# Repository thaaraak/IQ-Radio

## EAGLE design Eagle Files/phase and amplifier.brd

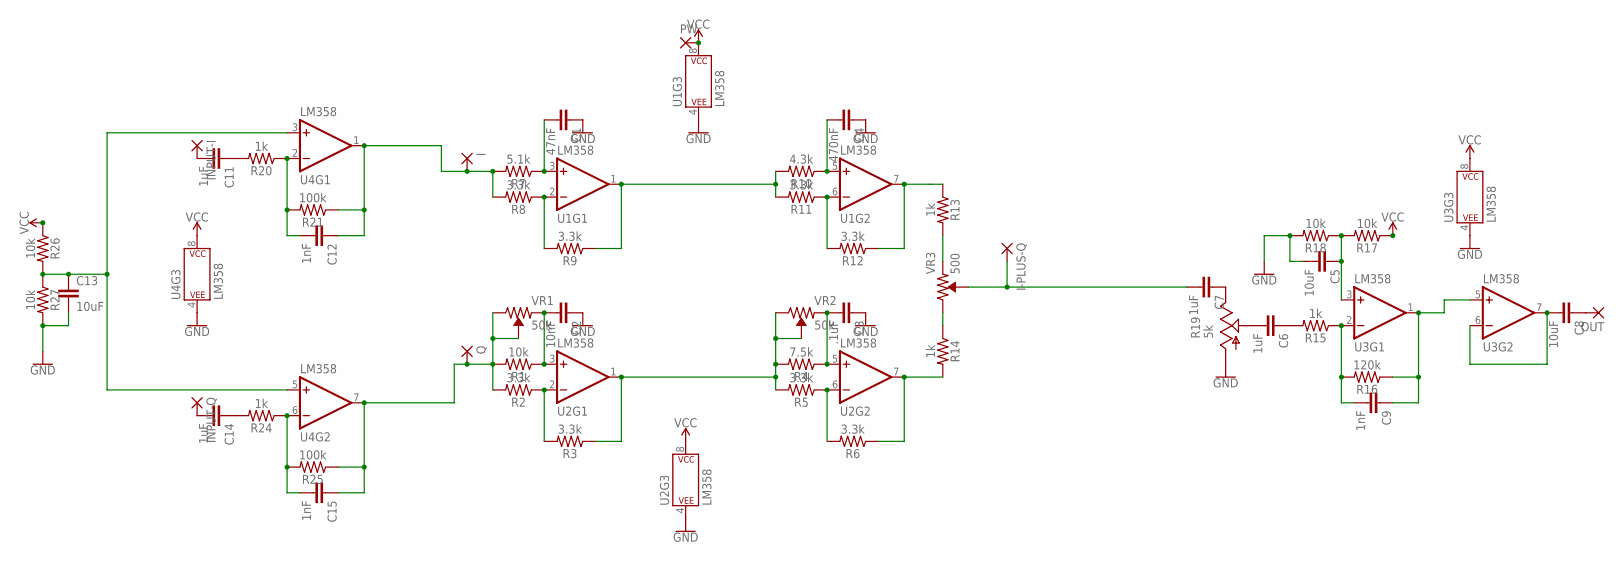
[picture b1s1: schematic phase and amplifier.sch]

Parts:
C1: 47nF; C5B3.5
C2: 10nF; C5B3.5
C3: .1uF; C5B3.5
C4: 470nF; C5B3.5
C5, C8, C13: 10uF; C5B3.5
C6, C7, C11, C14: 1uF; C5B3.5
C9, C12, C15: 1nF; C5B3.5
I: 2,54/1,1
I-PLUS-Q: 2,54/1,1
INPUT-I: 2,54/1,1
INPUT-Q: 2,54/1,1
OUT: 2,54/1,1
PW: 2,54/1,1
Q: 2,54/1,1
R1, R17, R18, R26, R27: 10k; AXIAL-0.3
R2, R3, R5, R6, R8, R9, R11, R12: 3.3k; AXIAL-0.3
R4: 7.5k; AXIAL-0.3
R7: 5.1k; AXIAL-0.3
R10: 4.3k; AXIAL-0.3
R13, R14, R15, R20, R24: 1k; AXIAL-0.3
R16: 120k; AXIAL-0.3
R19: 5k; B25V
R21, R25: 100k; AXIAL-0.3
U1, U2, U3, U4: LM358; DIP08
VR1, VR2: 50k; TRIMPOT-PTH-3386U
VR3: 500; TRIMPOT-PTH-3386U

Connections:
GND: C1.1, C2.1, C3.1, C4.1, C5.2, C13.2, R18.P$2 (2), R19.A, R27.P$2 (2), U1.4 (P$V-), U2.4 (P$V-), U3.4 (P$V-), U4.4 (P$V-)
unnamed: C2.2, R1.P$1 (1), U2.3 (+IN), VR1.1 (CCW)
unnamed: R2.P$1 (1), R3.P$2 (2), U2.2 (-IN)
unnamed: R3.P$1 (1), R4.P$2 (2), R5.P$2 (2), U2.1 (OUT), VR2.2 (WIPER), VR2.3 (CW)
unnamed: C13.1, R26.P$2 (2), R27.P$1 (1), U4.3 (+IN), U4.5 (+IN)
unnamed: C3.2, R4.P$1 (1), U2.5 (+IN), VR2.1 (CCW)
unnamed: R5.P$1 (1), R6.P$2 (2), U2.6 (-IN)
unnamed: R8.P$1 (1), R9.P$2 (2), U1.2 (-IN)
unnamed: R6.P$1 (1), R14.P$2 (2), U2.7 (OUT)
unnamed: C1.2, R7.P$1 (1), U1.3 (+IN)
unnamed: C14.2, INPUT-Q.1
unnamed: C4.2, R10.P$1 (1), U1.5 (+IN)
unnamed: R9.P$1 (1), R10.P$2 (2), R11.P$2 (2), U1.1 (OUT)
unnamed: R11.P$1 (1), R12.P$2 (2), U1.6 (-IN)
unnamed: R13.P$2 (2), VR3.1 (CCW)
unnamed: R12.P$1 (1), R13.P$1 (1), U1.7 (OUT)
unnamed: R14.P$1 (1), VR3.3 (CW)
unnamed: C7.2, I-PLUS-Q.1, VR3.2 (WIPER)
unnamed: C9.1, R16.P$1 (1), U3.1 (OUT), U3.5 (+IN)
unnamed: C9.2, R15.P$1 (1), R16.P$2 (2), U3.2 (-IN)
unnamed: C5.1, R17.P$2 (2), R18.P$1 (1), U3.3 (+IN)
unnamed: C6.1, R15.P$2 (2)
unnamed: C6.2, R19.S
unnamed: C7.1, R19.E
unnamed: C12.1, I.1, R7.P$2 (2), R8.P$2 (2), R21.P$1 (1), U4.1 (OUT)
unnamed: C8.2, U3.6 (-IN), U3.7 (OUT)
unnamed: C8.1, OUT.1
unnamed: C12.2, R20.P$1 (1), R21.P$2 (2), U4.2 (-IN)
unnamed: C11.2, INPUT-I.1
unnamed: C11.1, R20.P$2 (2)
unnamed: C15.1, Q.1, R1.P$2 (2), R2.P$2 (2), R25.P$1 (1), U4.7 (OUT), VR1.2 (WIPER), VR1.3 (CW)
unnamed: C15.2, R24.P$1 (1), R25.P$2 (2), U4.6 (-IN)
unnamed: C14.1, R24.P$2 (2)
VCC: PW.1, R17.P$1 (1), R26.P$1 (1), U1.8 (P$V+), U2.8 (P$V+), U3.8 (P$V+), U4.8 (P$V+)

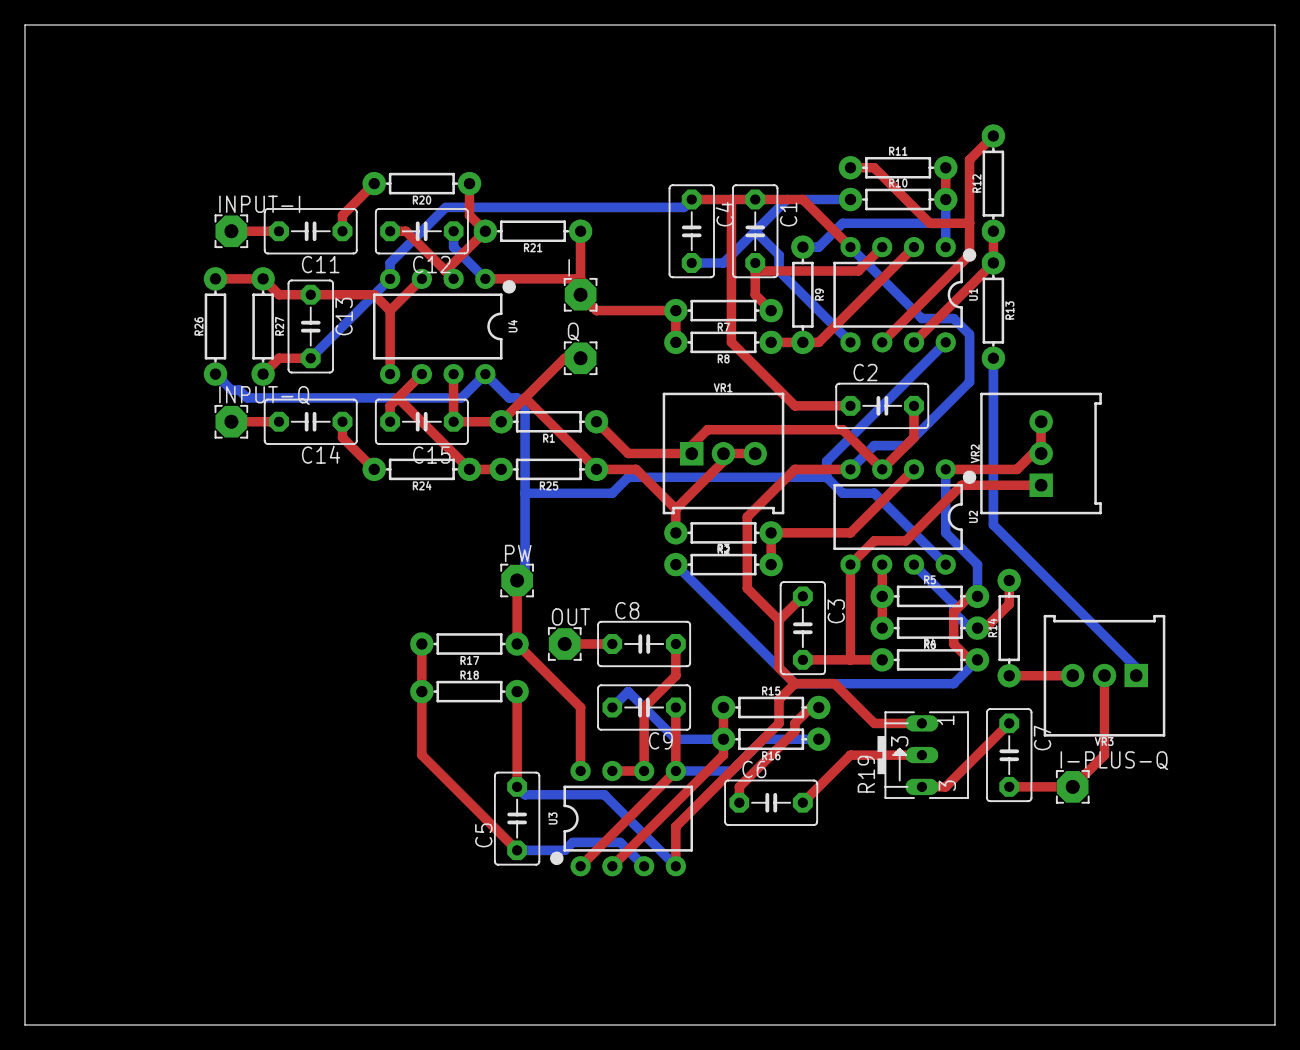
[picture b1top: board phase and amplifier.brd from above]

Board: 2 copper layers, 100.0 x 80.0 mm, 53 parts (0 on the bottom side), 34 nets.

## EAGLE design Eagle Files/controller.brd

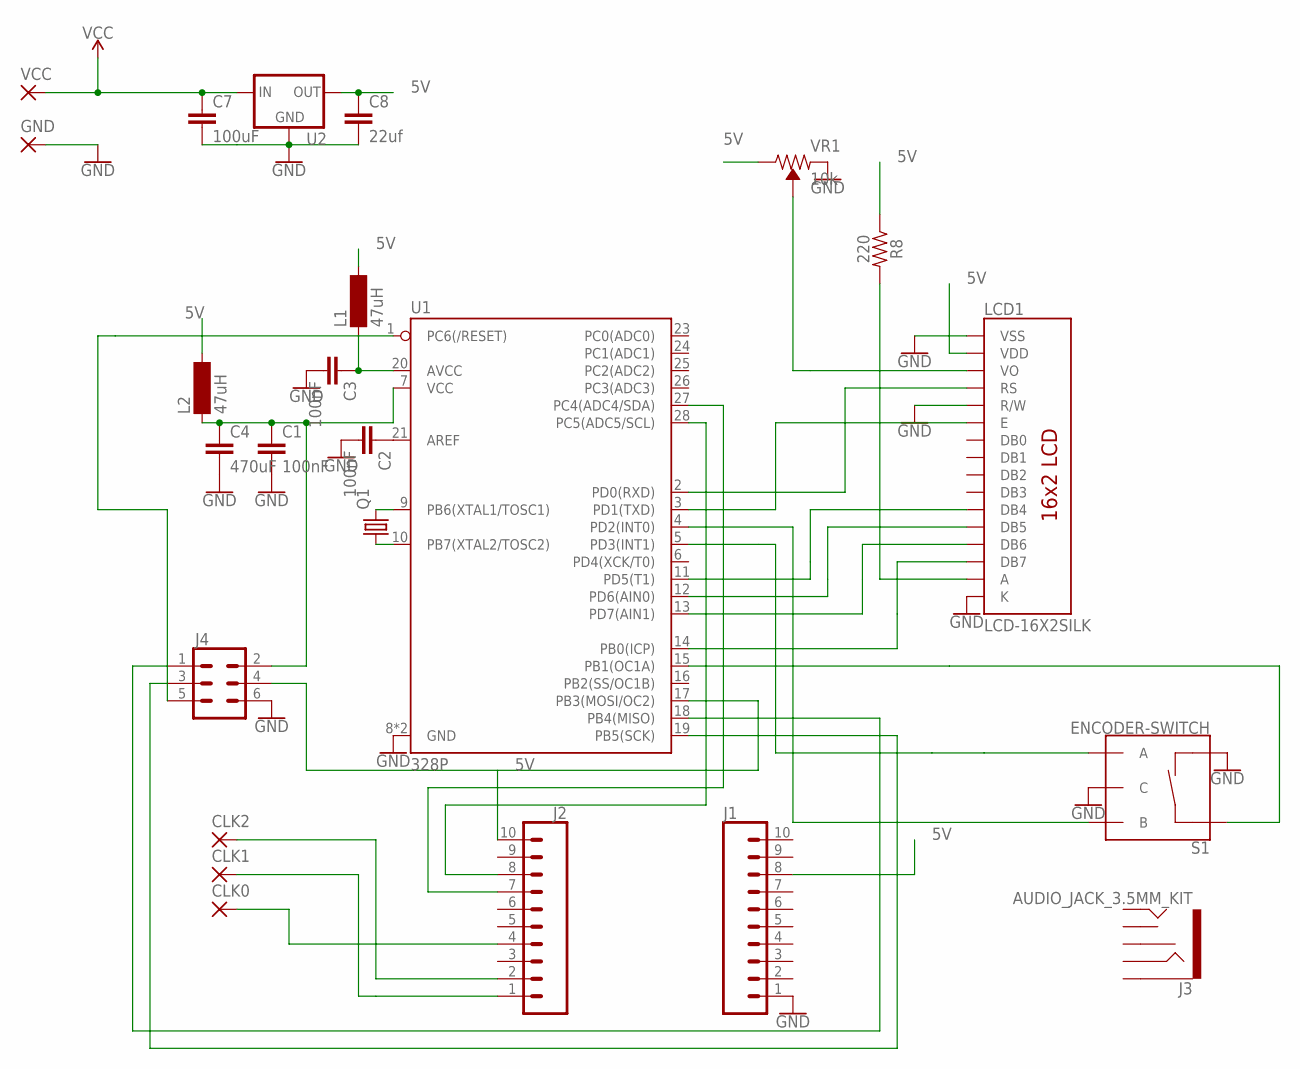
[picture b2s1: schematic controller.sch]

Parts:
C1, C2, C3: 100nF; C5B3.5
C4: 470uF; C5B3.5
C7: 100uF; C5B3.5
C8: 22uf; C5B3.5
CLK0, CLK1, CLK2: 3,17/1,1
GND: 3,17/1,1
J1, J2: CONN_10NO_SILK_PTH_FEMALE; 1X10_NO_SILK
J3: AUDIO_JACK_3.5MM_KIT; AUDIO-JACK-KIT
J4: CONN_03X2NO_SILK; 2X3-NS
L1, L2: 47uH; BS75
LCD1: LCD-16X2SILK; LCD-16X2
Q1: CRYTALHC49S; HC49/S
R8: 220; AXIAL-0.3
S1: ENCODER-SWITCH; ROTARY_ENC_PLAIN
U1: 328P; DIP28
U2: V_REG_78XXSINK; TO220-IGO
VCC: 3,17/1,1
VR1: 10k; TRIMPOT-PTH-3386U

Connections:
5V: C8.1, J1.8, J2.10, L1.2, L2.2, LCD1.2 (VDD), R8.P$1 (1), U2.OUT, VR1.3 (CW)
GND: C1.2, C2.2, C3.2, C4.2, C7.2, C8.2, GND.1, J1.1, J4.6, LCD1.1 (VSS), LCD1.5 (R/W), LCD1.16 (K), S1.C, S1.SW-, U1.8 (GND), U1.22 (GND), U2.GND, VR1.1 (CCW)
unnamed: C2.1, U1.21 (AREF)
unnamed: Q1.2, U1.9 (PB6(XTAL1/TOSC1))
unnamed: Q1.1, U1.10 (PB7(XTAL2/TOSC2))
unnamed: C1.1, C4.1, J4.2, L2.1, U1.7 (VCC)
unnamed: LCD1.14 (DB7), U1.14 (PB0(ICP))
unnamed: LCD1.13 (DB6), U1.13 (PD7(AIN1))
unnamed: S1.SW+, U1.15 (PB1(OC1A))
unnamed: LCD1.4 (RS), U1.2 (PD0(RXD))
unnamed: LCD1.12 (DB5), U1.12 (PD6(AIN0))
unnamed: LCD1.11 (DB4), U1.11 (PD5(T1))
unnamed: LCD1.3 (VO), VR1.2 (WIPER)
unnamed: LCD1.15 (A), R8.P$2 (2)
unnamed: CLK1.1, J2.1
unnamed: CLK2.1, J2.2
unnamed: CLK0.1, J2.4
unnamed: J2.8, U1.28 (PC5(ADC5/SCL))
unnamed: J2.7, U1.27 (PC4(ADC4/SDA))
unnamed: S1.A, U1.5 (PD3(INT1))
unnamed: S1.B, U1.4 (PD2(INT0))
unnamed: LCD1.6 (E), U1.3 (PD1(TXD))
unnamed: C3.1, L1.1, U1.20 (AVCC)
unnamed: J4.4, U1.17 (PB3(MOSI/OC2))
unnamed: J4.1, U1.18 (PB4(MISO))
unnamed: J4.3, U1.19 (PB5(SCK))
unnamed: J4.5, U1.1 (PC6(/RESET))
VCC: C7.1, U2.IN, VCC.1

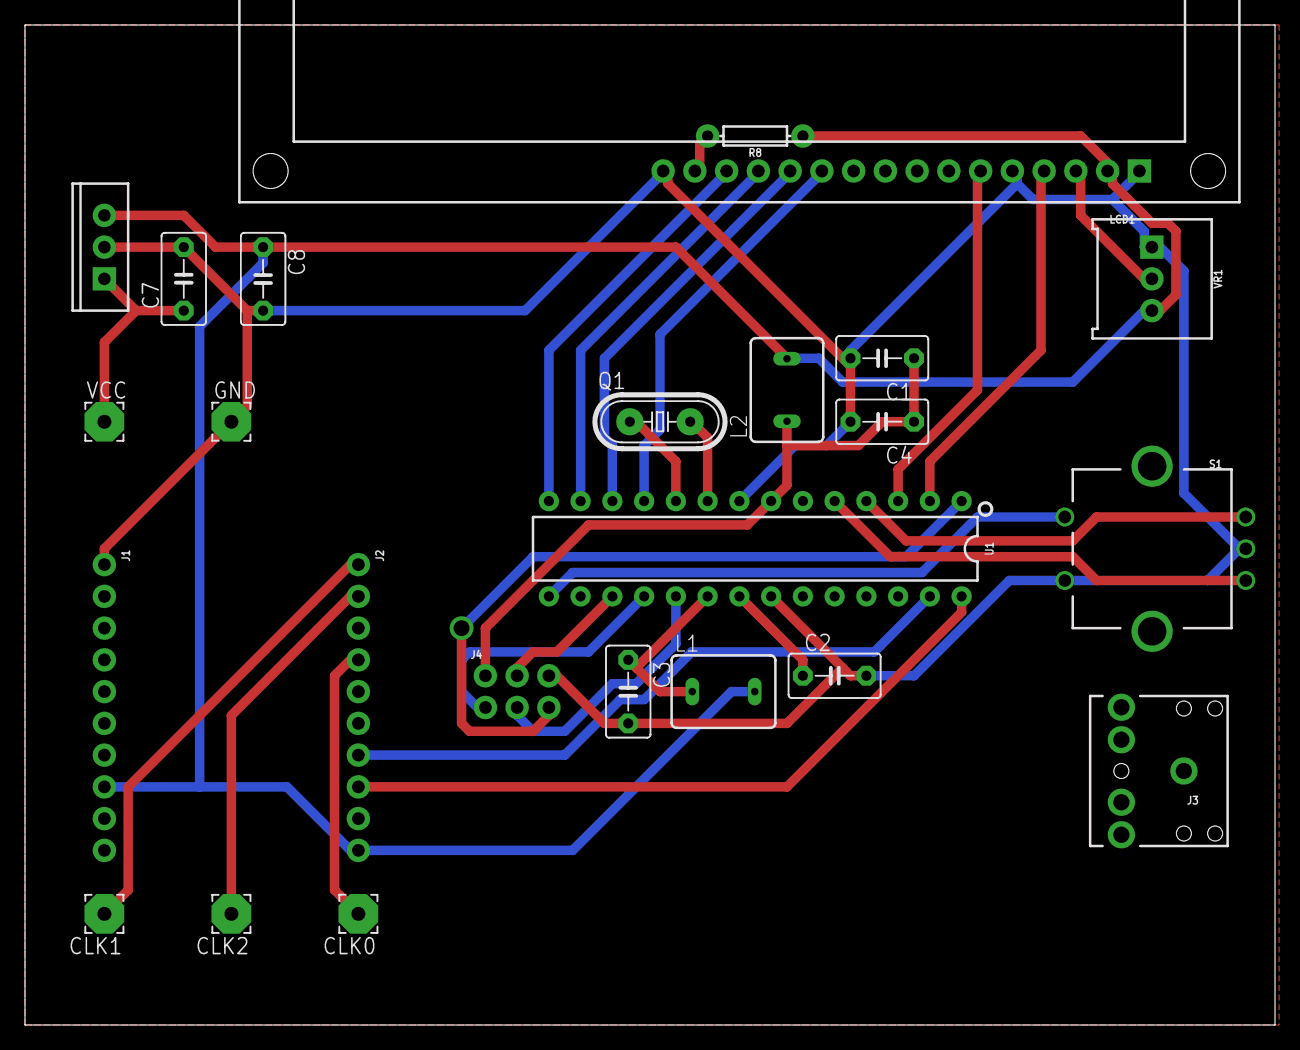
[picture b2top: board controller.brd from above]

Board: 2 copper layers, 100.0 x 80.0 mm, 24 parts (0 on the bottom side), 28 nets.

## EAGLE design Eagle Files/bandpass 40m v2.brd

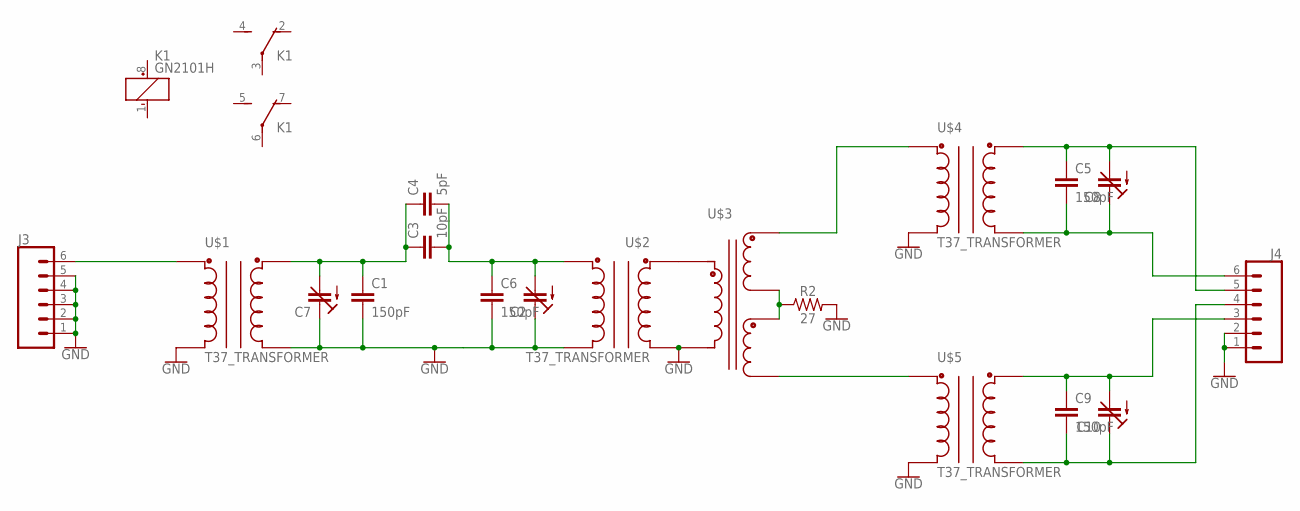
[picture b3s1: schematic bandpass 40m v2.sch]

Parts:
C1, C5, C6, C9: 150pF; C5B3.5
C2, C7, C8, C10: C-TRIMMTZ03; CTRIMTZ03
C3: 10pF; C5B3.5
C4: 5pF; C5B3.5
J3, J4: CONN_06SILK_FEMALE_PTH; 1X06
K1: GN2101H; GN
R2: 27; AXIAL-0.3
U$1, U$2, U$4, U$5: T37_TRANSFORMER
U$3: T50_SPLITTER

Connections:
GND: C1.2, C2.1 (E), C6.2, C7.1 (E), J3.1, J3.2, J3.3, J3.4, J3.5, J4.1, J4.2, R2.P$2 (2), U$1.C1A, U$1.C2A, U$2.C1A, U$2.C2A, U$3.C1A, U$4.C1A, U$5.C1A
GND1: C5.2, C8.1 (E), J4.6, U$4.C2A
GND2: C9.2, C10.1 (E), J4.4, U$5.C2A
unnamed: C1.1, C3.1, C4.1, C7.2 (A), U$1.C2B
unnamed: J3.6, U$1.C1B
unnamed: C2.2 (A), C3.2, C4.2, C6.1, U$2.C2B
unnamed: U$2.C1B, U$3.C1B
unnamed: U$3.C3B (C2B), U$4.C1B
unnamed: R2.P$1 (1), U$3.C2A (C3B), U$3.C3A (C2A)
unnamed: U$3.C2B (C3A), U$5.C1B
unnamed: C5.1, C8.2 (A), J4.5, U$4.C2B
unnamed: C9.1, C10.2 (A), J4.3, U$5.C2B

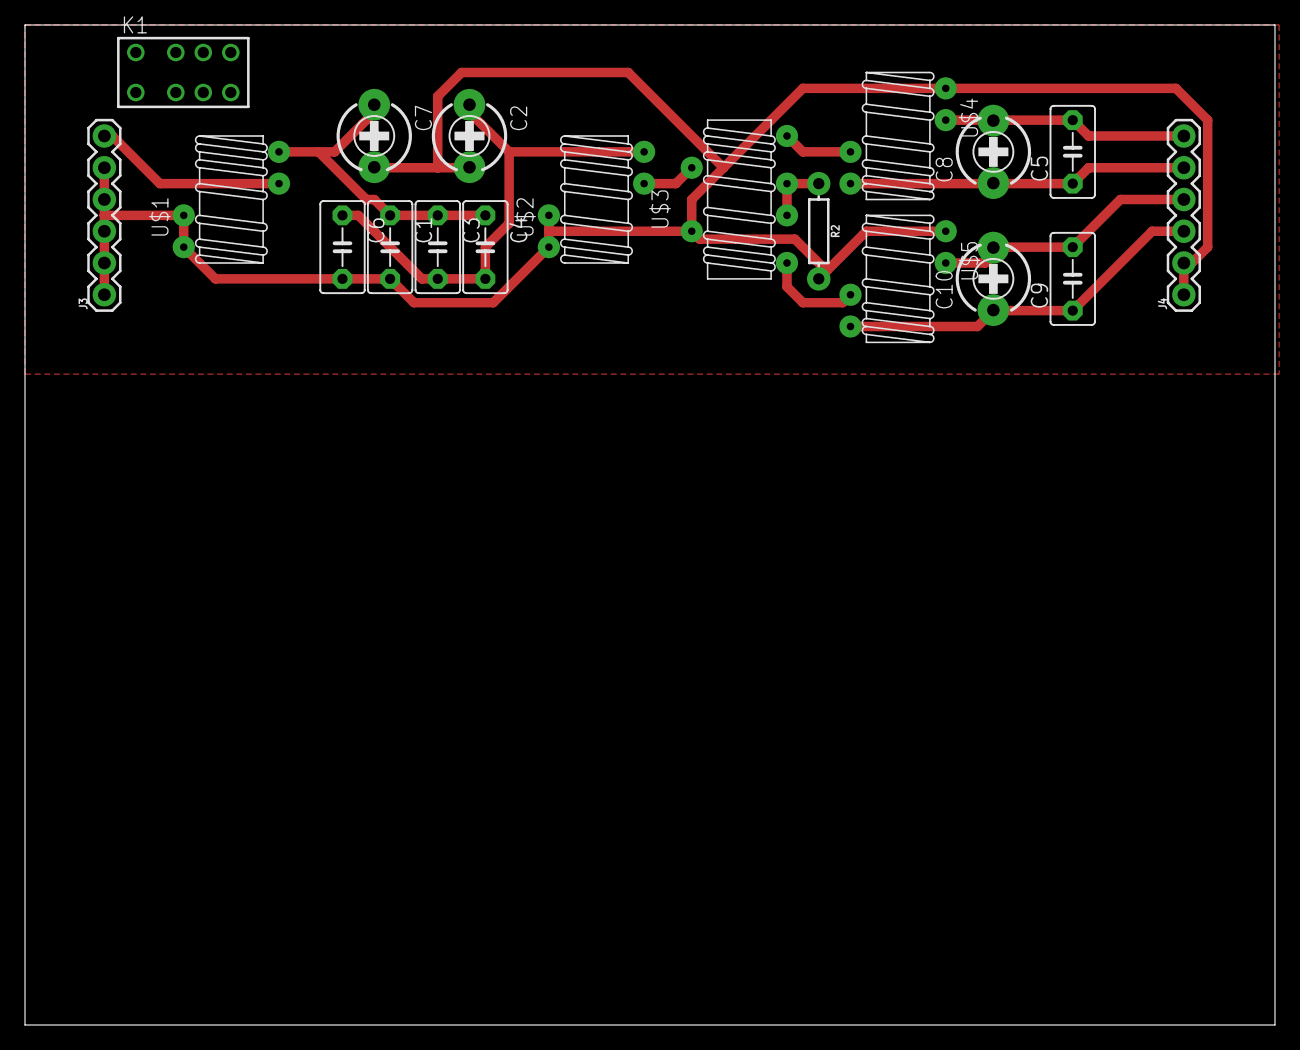
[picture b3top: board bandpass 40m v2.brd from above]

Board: 2 copper layers, 100.0 x 80.0 mm, 19 parts (0 on the bottom side), 12 nets.

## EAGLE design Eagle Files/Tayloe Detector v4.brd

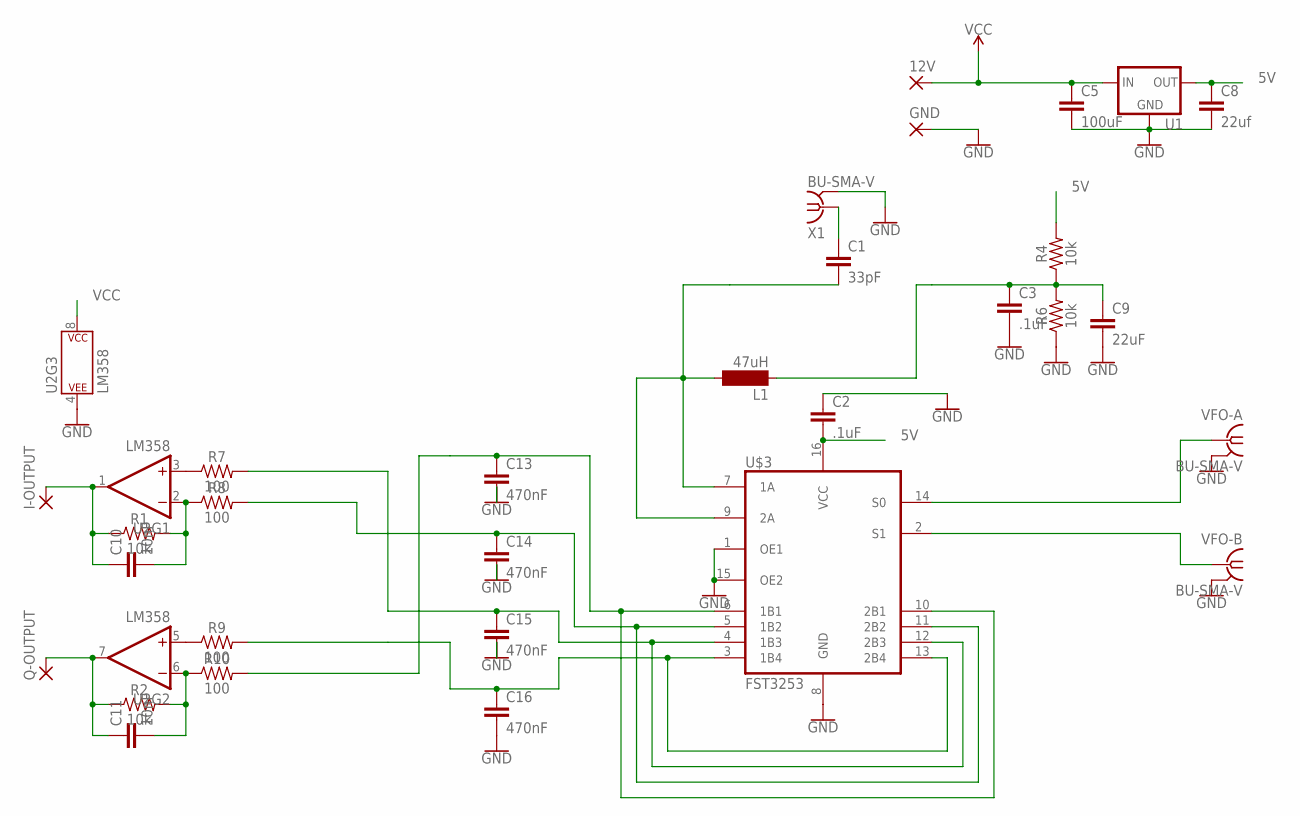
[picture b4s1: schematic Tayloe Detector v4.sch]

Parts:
12V: 3,17/1,1
C1: 33pF; C5B3.5
C2, C3: .1uF; C5B3.5
C5: 100uF; C5B3.5
C8: 22uf; C5B3.5
C9: 22uF; C5B3.5
C10, C11: 10nF; C5B3.5
C13, C14, C15, C16: 470nF; C5B3.5
GND: 3,17/1,1
I-OUTPUT: 3,17/1,1
L1: 47uH; BS75
Q-OUTPUT: 3,17/1,1
R1, R2, R4, R6: 10k; AXIAL-0.3
R7, R8, R9, R10: 100; AXIAL-0.3
U1: V_REG_78XXTO-92_UNTESTED; TO-92
U2: LM358; DIP08
U$3: FST3253; SO16
VFO-A: BU-SMA-V
VFO-B: BU-SMA-V
X1: BU-SMA-V

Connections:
5V: C2.2, C8.1, R4.P$2 (2), U1.1 (OUT), U$3.16 (VCC)
GND: C2.1, C3.2, C5.2, C8.2, C9.2, C13.2, C14.2, C15.2, C16.2, GND.1, R6.P$1 (1), U1.2 (GND), U2.4 (P$V-), U$3.1 (OE1), U$3.8 (GND), U$3.15 (OE2), VFO-A.2, VFO-A.3 (2), VFO-A.4 (2), VFO-A.5 (2), VFO-B.2, VFO-B.3 (2), VFO-B.4 (2), VFO-B.5 (2), X1.2, X1.3 (2), X1.4 (2), X1.5 (2)
unnamed: C1.1, X1.1
unnamed: R7.P$1 (1), U2.3 (+IN)
unnamed: C3.1, C9.1, L1.1, R4.P$1 (1), R6.P$2 (2)
unnamed: C1.2, L1.2, U$3.7 (1A), U$3.9 (2A)
unnamed: C10.2, R1.P$2 (2), R8.P$1 (1), U2.2 (-IN)
unnamed: R9.P$1 (1), U2.5 (+IN)
unnamed: C10.1, I-OUTPUT.1, R1.P$1 (1), U2.1 (OUT)
unnamed: C14.1, R8.P$2 (2), U$3.5 (1B2), U$3.11 (2B2)
unnamed: C11.2, R2.P$2 (2), R10.P$1 (1), U2.6 (-IN)
unnamed: C15.1, R7.P$2 (2), U$3.4 (1B3), U$3.12 (2B3)
unnamed: C13.1, R10.P$2 (2), U$3.6 (1B1), U$3.10 (2B1)
unnamed: U$3.14 (S0), VFO-A.1
unnamed: C11.1, Q-OUTPUT.1, R2.P$1 (1), U2.7 (OUT)
unnamed: U$3.2 (S1), VFO-B.1
unnamed: C16.1, R9.P$2 (2), U$3.3 (1B4), U$3.13 (2B4)
VCC: 12V.1, C5.1, U1.3 (IN), U2.8 (P$V+)

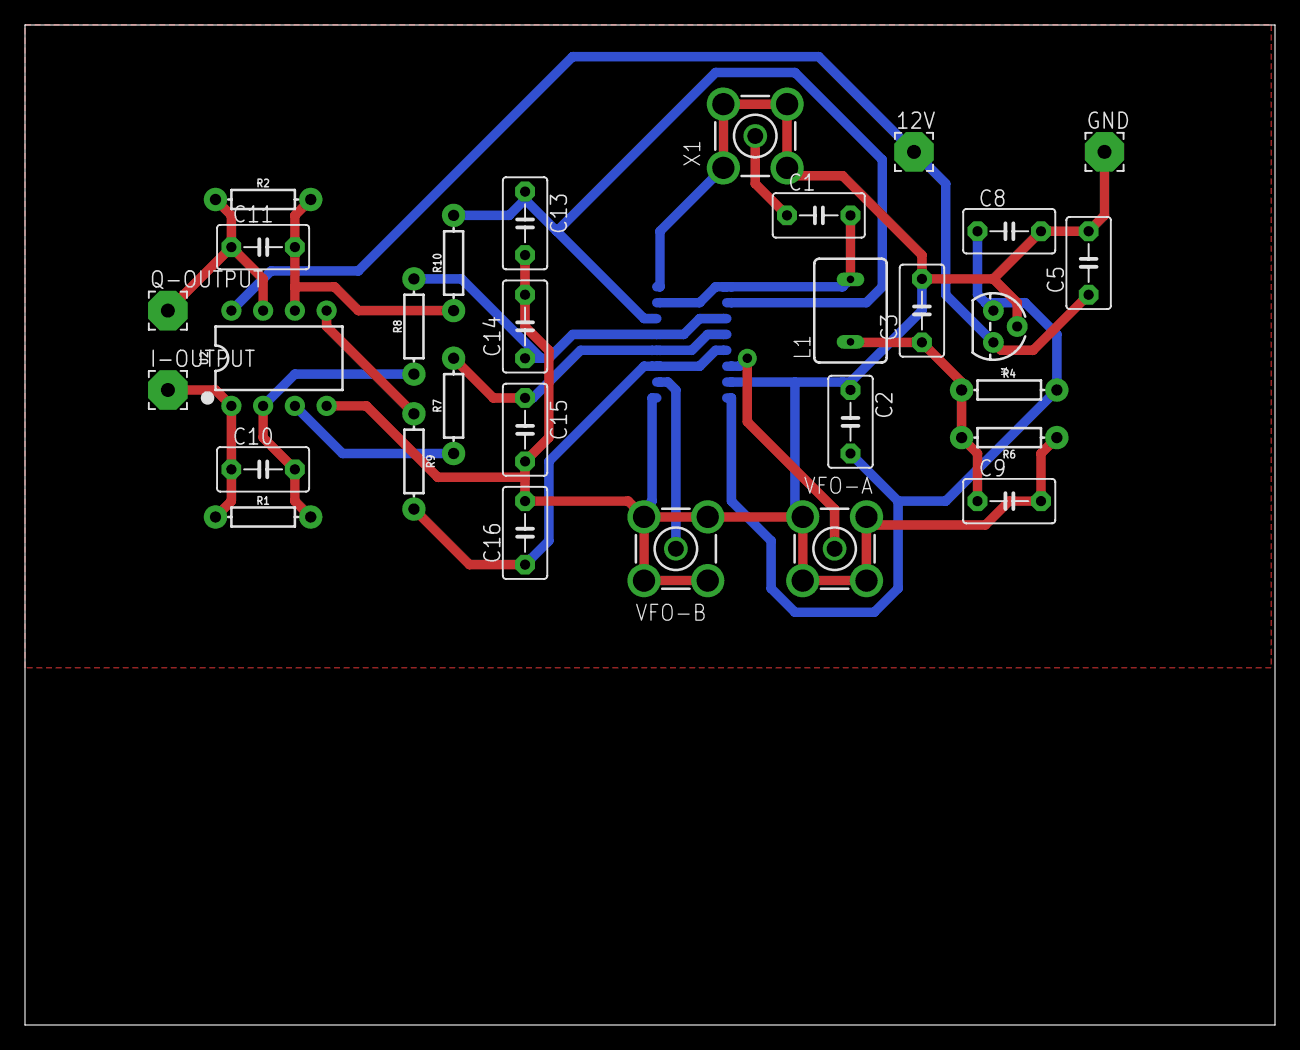
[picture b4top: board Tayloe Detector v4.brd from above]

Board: 2 copper layers, 100.0 x 80.0 mm, 31 parts (1 on the bottom side), 18 nets.

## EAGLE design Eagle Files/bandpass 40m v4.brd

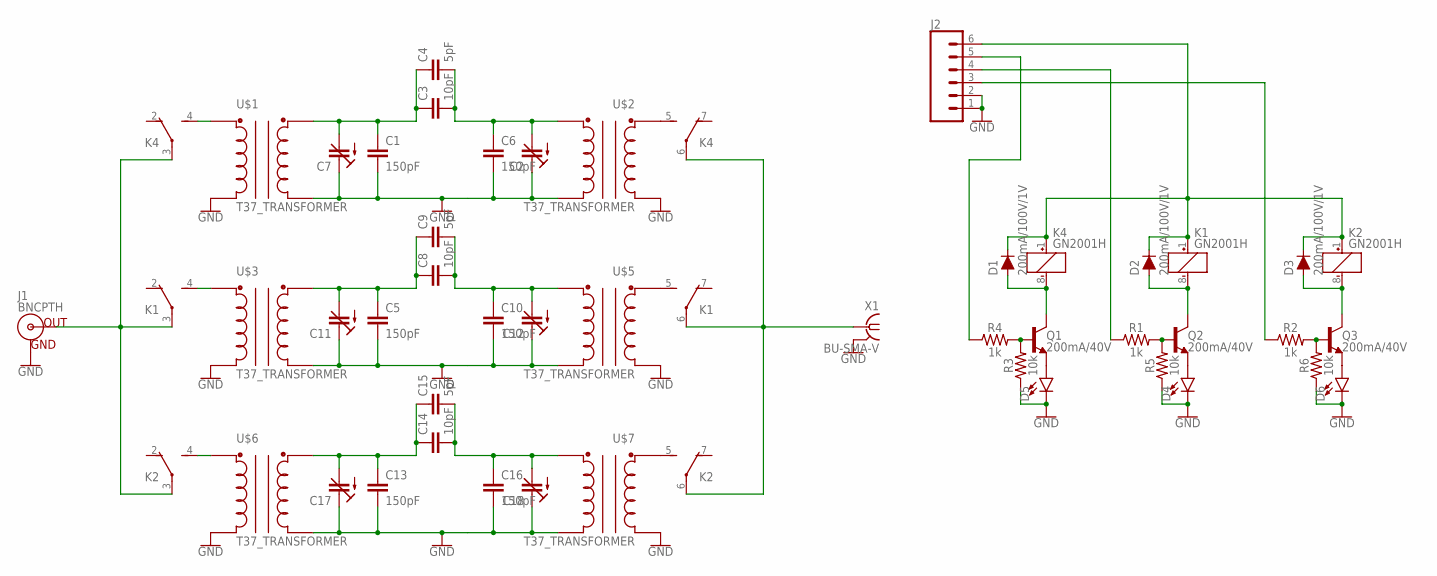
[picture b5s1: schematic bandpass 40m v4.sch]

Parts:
C1, C5, C6, C10, C13, C16: 150pF; C5B3.5
C2, C7, C11, C12, C17, C18: C-TRIMMTZ03; CTRIMTZ03
C3, C8, C14: 10pF; C5B3.5
C4, C9, C15: 5pF; C5B3.5
D1, D2, D3: 200mA/100V/1V; DIODE-1N4148
D4, D5, D6: LED5MM; LED_5MM
J1: BNCPTH; BNC
J2: CONN_06LONGPADS; 1X06_LONGPADS
K1, K2, K4: GN2001H; GN
Q1, Q2, Q3: 200mA/40V; TO-92
R1, R2, R4: 1k; AXIAL-0.3
R3, R5, R6: 10k; AXIAL-0.3
U$1, U$2, U$3, U$5, U$6, U$7: T37_TRANSFORMER
X1: BU-SMA-V

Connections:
GND: C1.2, C2.1 (E), C5.2, C6.2, C7.1 (E), C10.2, C11.1 (E), C12.1 (E), C13.2, C16.2, C17.1 (E), C18.1 (E), D4.K (C), D5.K (C), D6.K (C), J1.GND, J2.1, J2.2, R3.P$1 (1), R5.P$1 (1), R6.P$1 (1), U$1.C1A, U$1.C2A, U$2.C1A, U$2.C2A, U$3.C1A, U$3.C2A, U$5.C1A, U$5.C2A, U$6.C1A, U$6.C2A, U$7.C1A, U$7.C2A, X1.2, X1.3 (2), X1.4 (2), X1.5 (2)
unnamed: C1.1, C3.1, C4.1, C7.2 (A), U$1.C2B
unnamed: K4.4 (S), U$1.C1B
unnamed: C2.2 (A), C3.2, C4.2, C6.1, U$2.C2B
unnamed: K1.6, K2.6, K4.6, X1.1
unnamed: K4.5 (S), U$2.C1B
unnamed: C5.1, C8.1, C9.1, C11.2 (A), U$3.C2B
unnamed: C8.2, C9.2, C10.1, C12.2 (A), U$5.C2B
unnamed: K1.4 (S), U$3.C1B
unnamed: K1.5 (S), U$5.C1B
unnamed: C13.1, C14.1, C15.1, C17.2 (A), U$6.C2B
unnamed: C14.2, C15.2, C16.1, C18.2 (A), U$7.C2B
unnamed: J1.S (OUT), K1.3, K2.3, K4.3
unnamed: K2.5 (S), U$7.C1B
unnamed: K2.4 (S), U$6.C1B
unnamed: D1.A, K4.8 (-), Q1.3 (C)
unnamed: D2.A, K1.8 (-), Q2.3 (C)
unnamed: D3.A, K2.8 (-), Q3.3 (C)
unnamed: D5.A, Q1.1 (E)
unnamed: J2.5, R4.P$1 (1)
unnamed: J2.4, R1.P$1 (1)
unnamed: J2.3, R2.P$1 (1)
unnamed: D1.C, D2.C, D3.C, J2.6, K1.1 (+), K2.1 (+), K4.1 (+)
unnamed: D4.A, Q2.1 (E)
unnamed: D6.A, Q3.1 (E)
unnamed: Q1.2 (B), R3.P$2 (2), R4.P$2 (2)
unnamed: Q2.2 (B), R1.P$2 (2), R5.P$2 (2)
unnamed: Q3.2 (B), R2.P$2 (2), R6.P$2 (2)

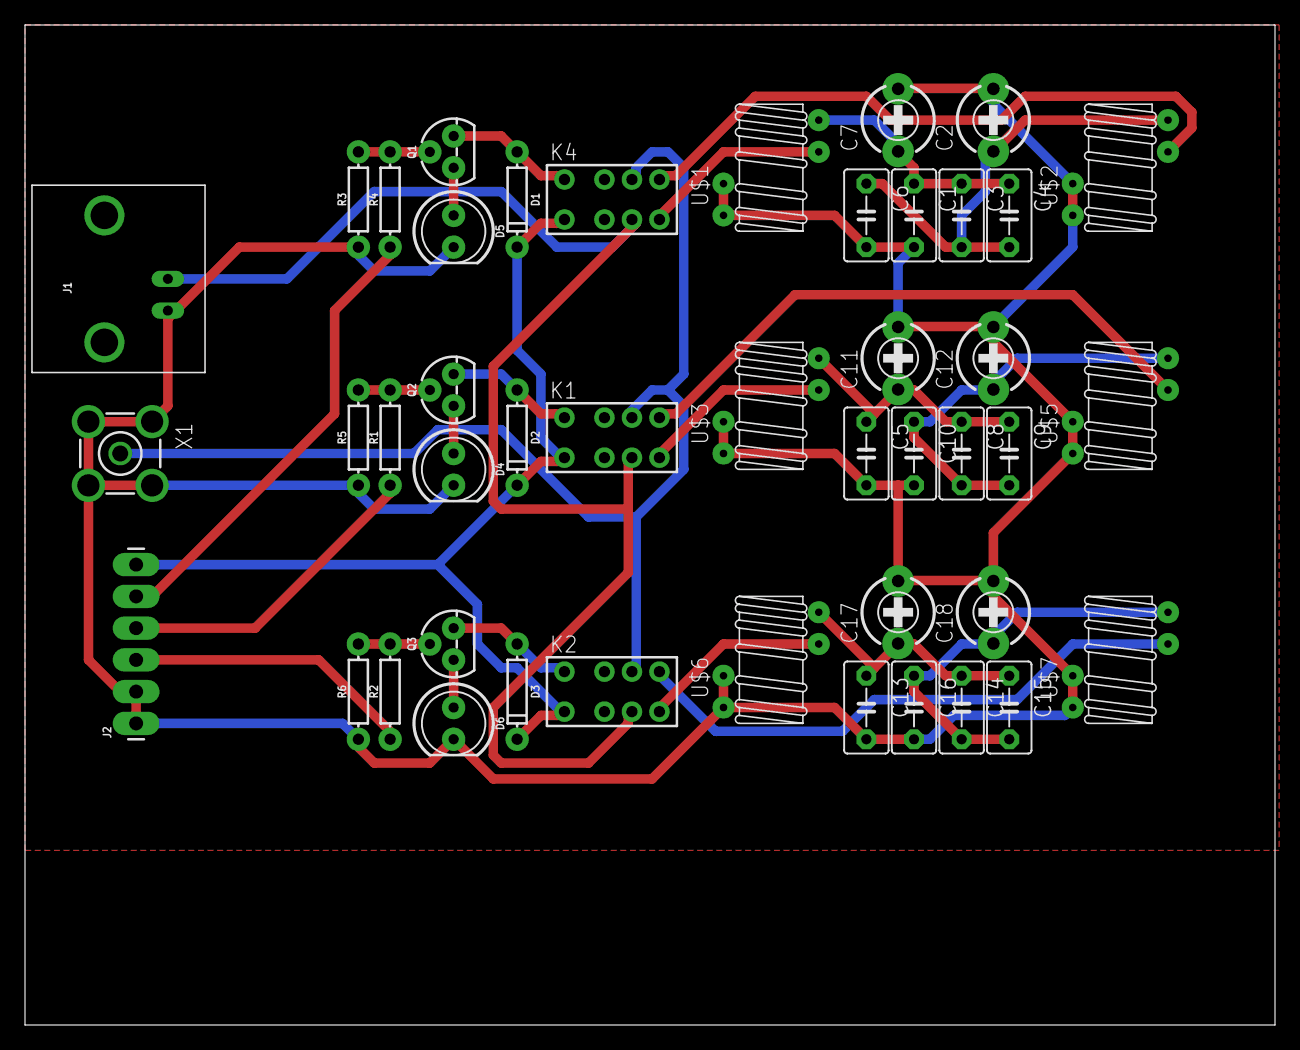
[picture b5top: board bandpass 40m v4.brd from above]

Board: 2 copper layers, 100.0 x 80.0 mm, 45 parts (0 on the bottom side), 28 nets.

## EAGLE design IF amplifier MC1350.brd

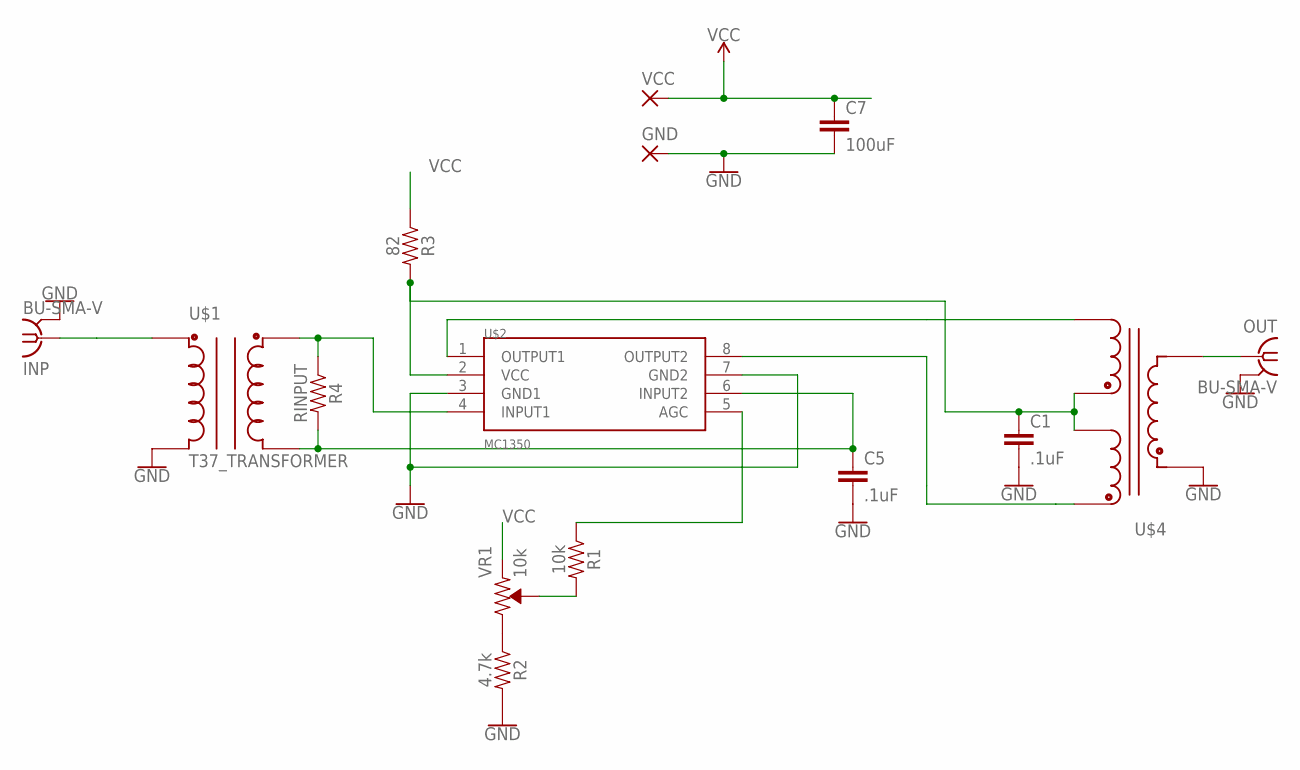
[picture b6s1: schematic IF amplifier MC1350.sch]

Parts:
C1, C5: .1uF; C5B3.5
C7: 100uF; C5B3.5
GND: 3,17/1,1
INP: BU-SMA-V
OUT: BU-SMA-V
R1: 10k; AXIAL-0.3
R2: 4.7k; AXIAL-0.3
R3: 82; AXIAL-0.3
R4: RINPUT; AXIAL-0.3
U$1: T37_TRANSFORMER
U$2: MC1350; DIP8
U$4: T50_SPLITTER
VCC: 3,17/1,1
VR1: 10k; TRIMPOT-PTH-3386U

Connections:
GND: C1.2, C5.2, C7.2, GND.1, INP.2, INP.3 (2), INP.4 (2), INP.5 (2), OUT.2, OUT.3 (2), OUT.4 (2), OUT.5 (2), R2.P$2 (2), U$1.C1A, U$2.3 (GND1), U$2.7 (GND2), U$4.C1B
unnamed: R4.P$1 (1), U$1.C2B, U$2.4 (INPUT1)
unnamed: U$2.1 (OUTPUT1), U$4.C2B (C3A)
unnamed: R2.P$1 (1), VR1.3 (CW)
unnamed: OUT.1, U$4.C1A
unnamed: C1.1, R3.P$2 (2), U$2.2 (VCC), U$4.C2A (C3B), U$4.C3A (C2A)
unnamed: U$2.8 (OUTPUT2), U$4.C3B (C2B)
unnamed: C5.1, R4.P$2 (2), U$1.C2A, U$2.6 (INPUT2)
unnamed: INP.1, U$1.C1B
unnamed: R1.P$1 (1), U$2.5 (AGC)
unnamed: R1.P$2 (2), VR1.2 (WIPER)
VCC: C7.1, R3.P$1 (1), VCC.1, VR1.1 (CCW)

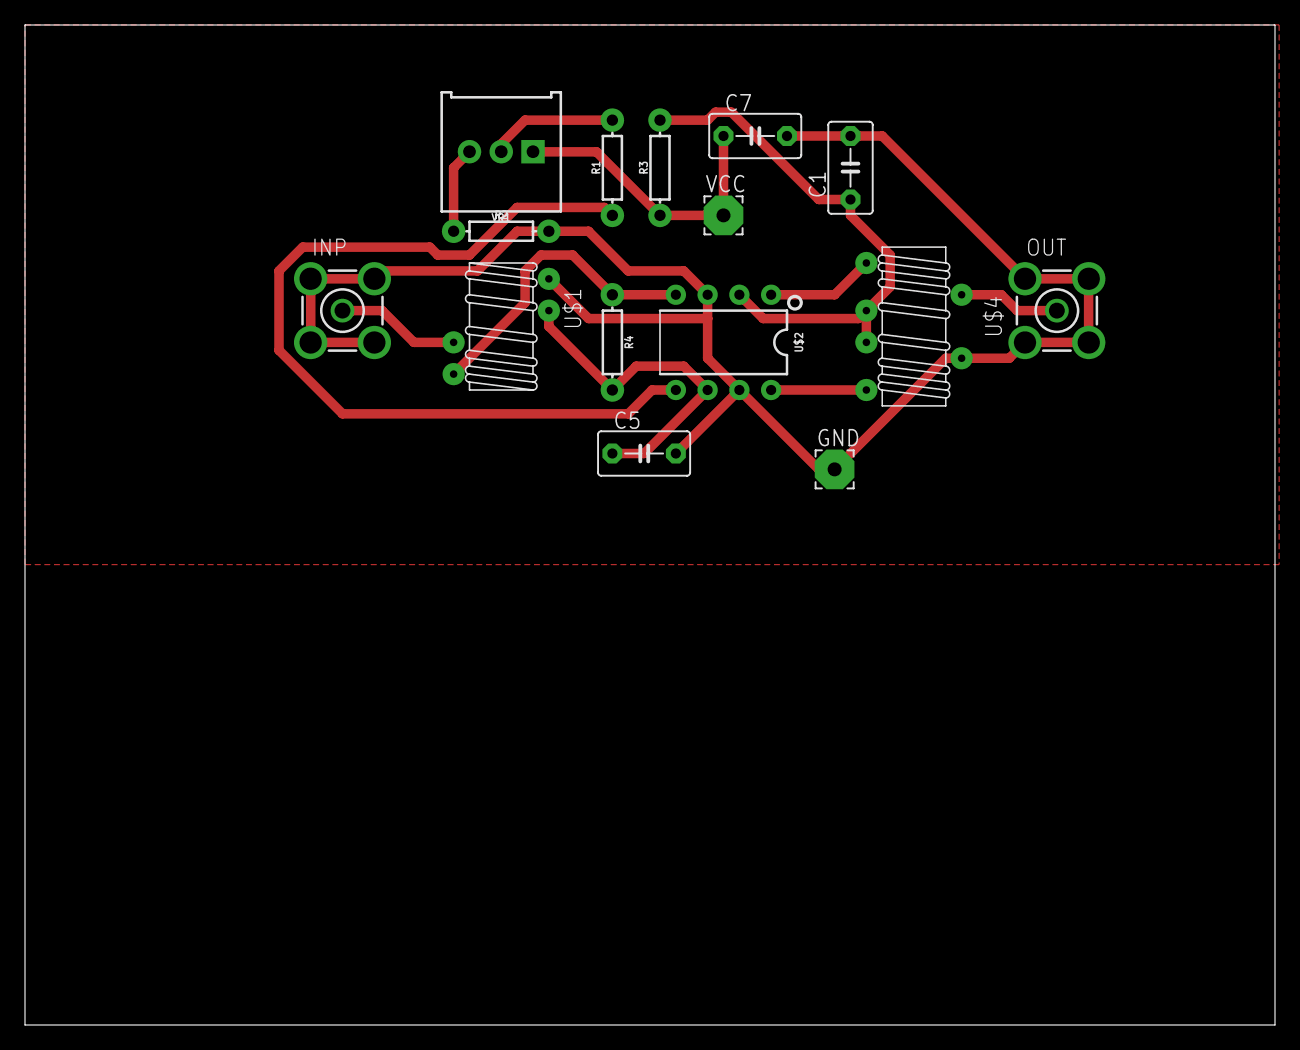
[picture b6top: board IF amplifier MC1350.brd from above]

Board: 2 copper layers, 100.0 x 80.0 mm, 15 parts (0 on the bottom side), 12 nets.

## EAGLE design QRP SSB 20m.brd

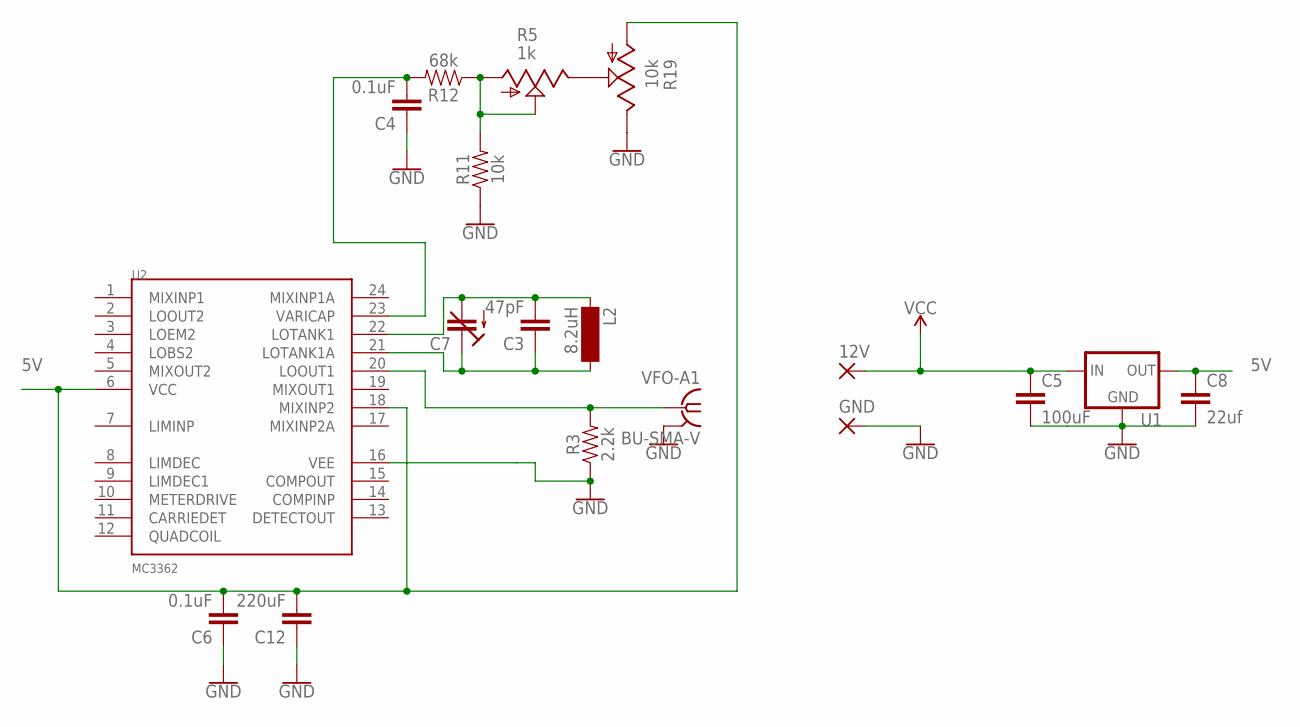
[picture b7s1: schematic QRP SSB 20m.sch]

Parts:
12V: 3,17/1,1
C3: 47pF; C5B3.5
C4, C6: 0.1uF; C5B3.5
C5: 100uF; C5B3.5
C7: C-TRIMMTZ03; CTRIMTZ03
C8: 22uf; C5B3.5
C12: 220uF; C5B3.5
GND: 3,17/1,1
L2: 8.2uH; BS75
R3: 2.2k; AXIAL-0.3
R5: 1k; B25V
R11: 10k; AXIAL-0.3
R12: 68k; AXIAL-0.3
R19: 10k; B25V
U1: V_REG_78XXTO-92_UNTESTED; TO-92
U2: MC3362; DIP24
VFO-A1: BU-SMA-V

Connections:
5V: C6.2, C8.1, C12.2, R19.A, U1.1 (OUT), U2.6 (VCC), U2.18 (MIXINP2)
GND: C4.1, C5.2, C6.1, C8.2, C12.1, GND.1, R3.P$1 (1), R11.P$1 (1), R19.E, U1.2 (GND), U2.16 (VEE), VFO-A1.2, VFO-A1.3 (2), VFO-A1.4 (2), VFO-A1.5 (2)
unnamed: C3.1, C7.1 (E), L2.2, U2.21 (LOTANK1A)
unnamed: C3.2, C7.2 (A), L2.1, U2.22 (LOTANK1)
unnamed: R3.P$2 (2), U2.20 (LOOUT1), VFO-A1.1
unnamed: R5.E, R19.S
unnamed: R5.A, R5.S, R11.P$2 (2), R12.P$1 (1)
unnamed: C4.2, R12.P$2 (2), U2.23 (VARICAP)
VCC: 12V.1, C5.1, U1.3 (IN)

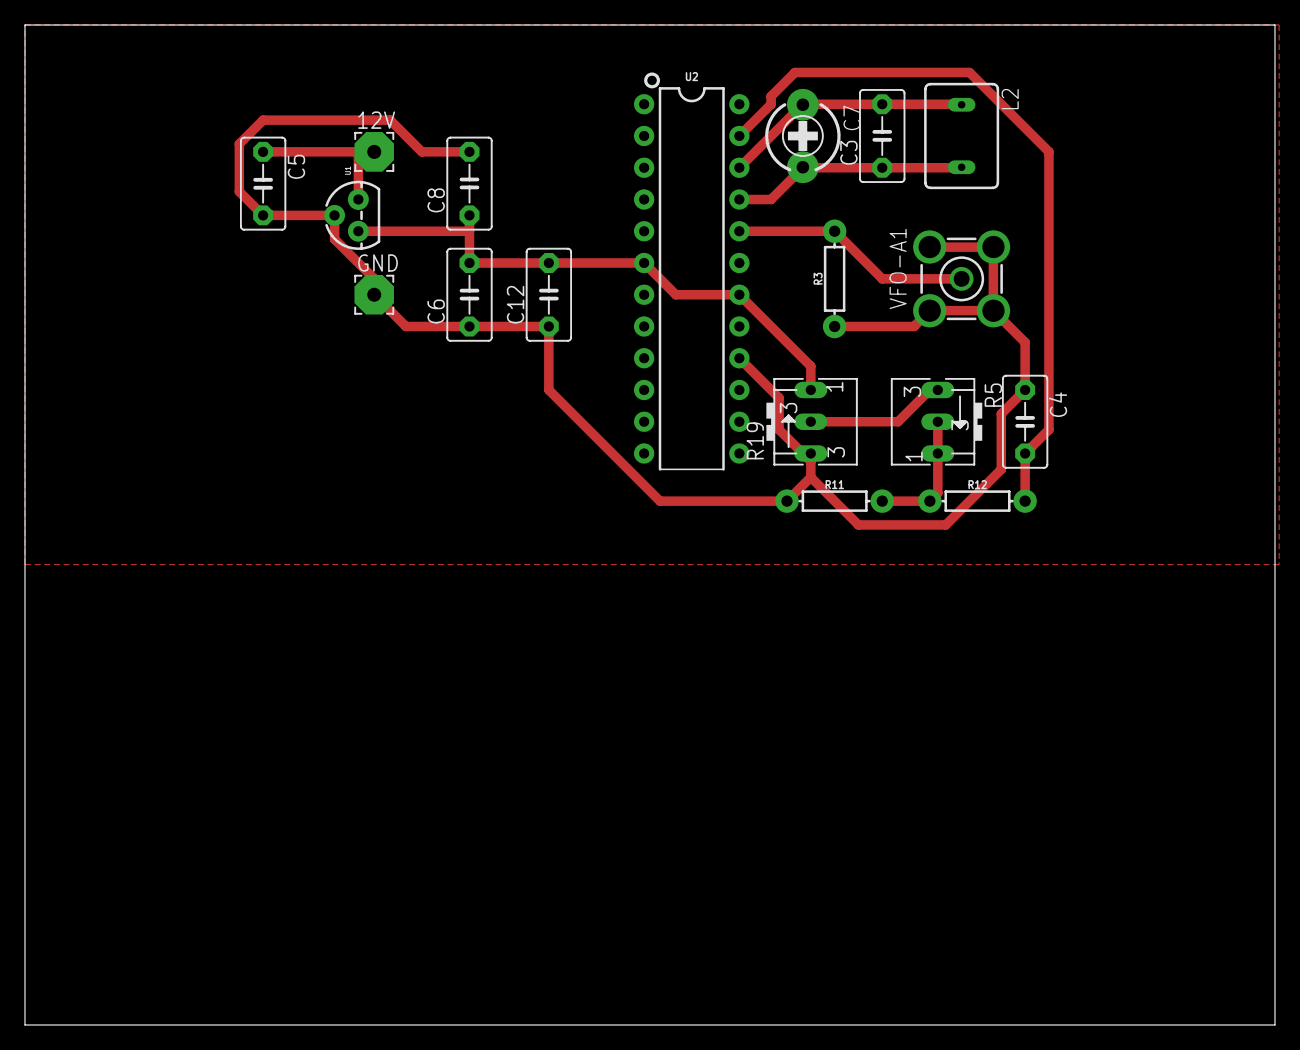
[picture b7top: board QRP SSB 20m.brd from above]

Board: 2 copper layers, 100.0 x 80.0 mm, 18 parts (0 on the bottom side), 9 nets.

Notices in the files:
parts and their libraries:
SparkFun-IC-Power: Licensing: Creative Commons ShareAlike 4.0 International - https://creativecommons.org/licenses/by-sa/4.0
